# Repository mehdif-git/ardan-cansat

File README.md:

## SCALAR-VI CANSAT *Ardan*

## Description
Code and schematics of the cansat aboard SCALAR-VI made with students of the Jules Verne middleschool in Carcassone, FR.

## Installation
The ‘RadioHead’ library used to manage the LoRaWAN depends on “stdatomic”, we need to change the source code of ‘RadioHead’ to source the correct implementation for Arduino vs. ESP.

## Contributing
This work is common to the Supaero Space Section's Scalar project. Any project member is allowed to contribute.

## Authors and acknowledgment
Electronics has been made with the help of F. Topeza and C. Mopin-Rauschkolb.
CAD has been done entierly by D. Bessede

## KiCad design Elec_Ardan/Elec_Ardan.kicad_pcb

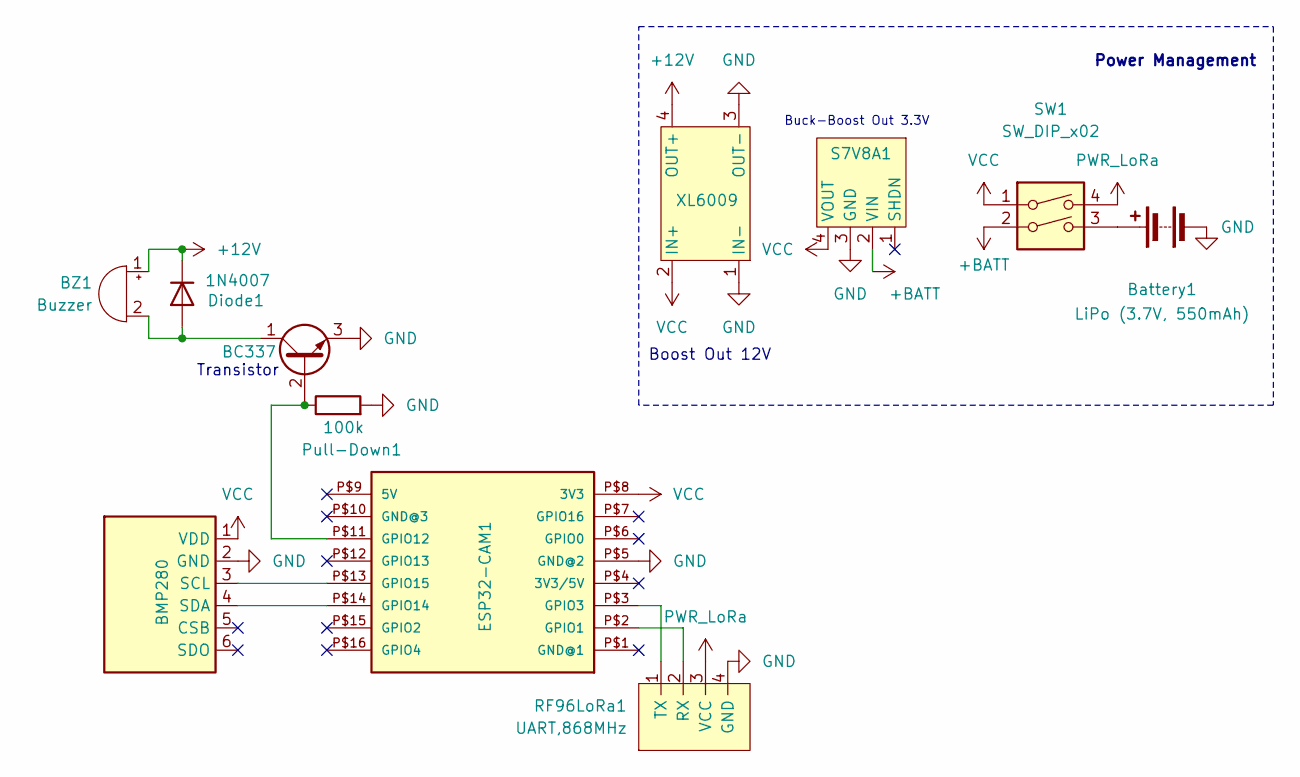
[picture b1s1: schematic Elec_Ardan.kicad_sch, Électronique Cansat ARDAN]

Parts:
BMP280: BMP280
BZ1: Buzzer; JST_XH_B2B-XH-A_1x02_P2.50mm_Vertical
Battery1: LiPo (3.7V, 550mAh); JST_XH_B2B-XH-A_1x02_P2.50mm_Vertical
Diode1: 1N4007; D_DO-41_SOD81_P10.16mm_Horizontal
ESP32-CAM1: ESP32-CAM
Pull-Down1: 100k; R_Axial_DIN0309_L9.0mm_D3.2mm_P12.70mm_Horizontal
Q1: BC337; TO-92_Inline
RF96LoRa1: UART,868MHz; JST_XH_B4B-XH-A_1x04_P2.50mm_Vertical
S7V8A1: S7V8A1
SW1: SW_DIP_x02; JST_XH_B4B-XH-A_1x04_P2.50mm_Vertical
XL6009: XL6009

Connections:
+12V: BZ1.1 (+), Diode1.1 (K), XL6009.4 (OUT+)
+BATT: S7V8A1.2 (VIN), SW1.2
GND: BMP280.2 (GND), Battery1.2 (-), ESP32-CAM1.P$5 (GND@2), Pull-Down1.2, Q1.3 (E), RF96LoRa1.4 (GND), S7V8A1.3 (GND), XL6009.1 (IN-), XL6009.3 (OUT-)
unnamed: BMP280.3 (SCL), ESP32-CAM1.P$13 (GPIO15)
unnamed: BMP280.4 (SDA), ESP32-CAM1.P$14 (GPIO14)
unnamed: BZ1.2 (-), Diode1.2 (A), Q1.1 (C)
unnamed: Battery1.1 (+), SW1.3
unnamed: ESP32-CAM1.P$2 (GPIO1), RF96LoRa1.2 (RX)
unnamed: ESP32-CAM1.P$3 (GPIO3), RF96LoRa1.1 (TX)
unnamed: ESP32-CAM1.P$11 (GPIO12), Pull-Down1.1, Q1.2 (B)
PWR_LoRa: RF96LoRa1.3 (VCC), SW1.4
VCC: BMP280.1 (VDD), ESP32-CAM1.P$8 (3V3), S7V8A1.4 (VOUT), SW1.1, XL6009.2 (IN+)

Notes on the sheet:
Power Management
Buck-Boost Out 3.3V
Boost Out 12V
Transistor

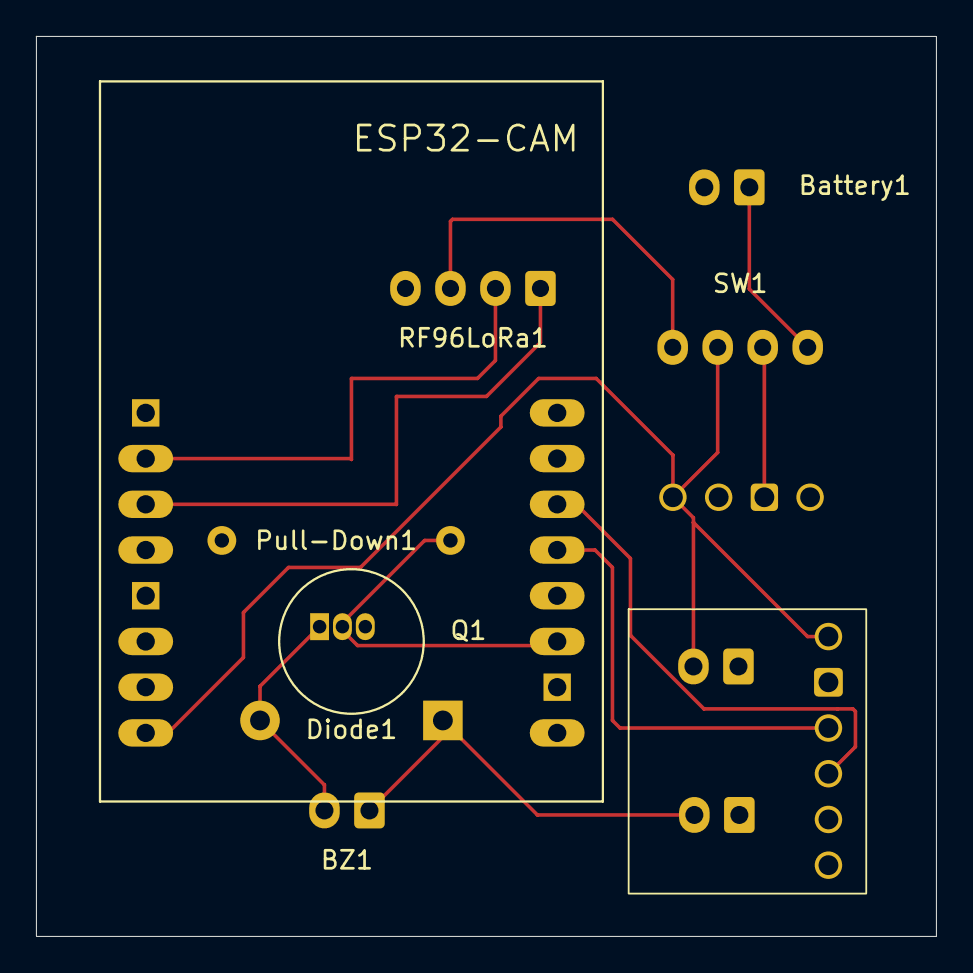
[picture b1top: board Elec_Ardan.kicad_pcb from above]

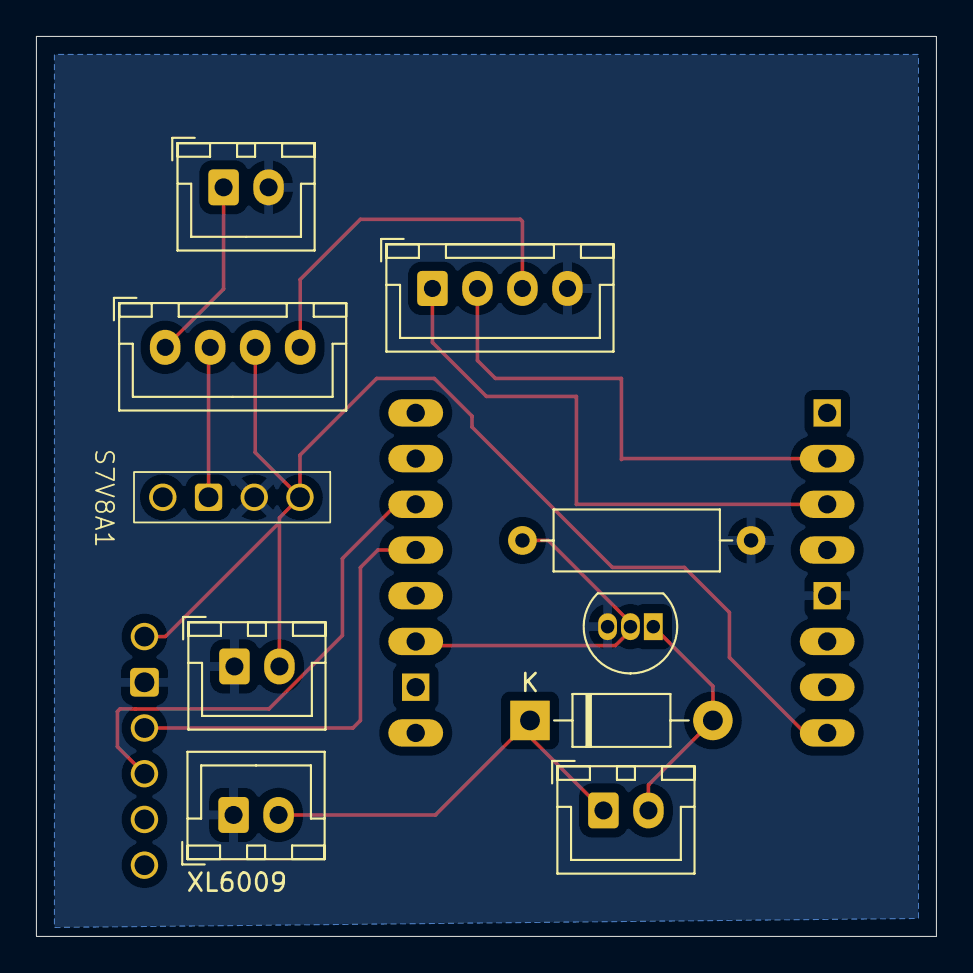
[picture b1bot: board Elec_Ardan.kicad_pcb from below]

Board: 2 copper layers, 50.0 x 50.0 mm, 11 parts (9 on the bottom side), 12 nets.

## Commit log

2025-01-27 Initial commit.
2025-01-27 Edited README with basic info.
2025-03-02 Final beta code.
2025-03-03 Arduino code.
2025-06-03 Version du projet 3 juin 2025.
2025-06-03 Ajout du fichier STEP de la carte entière
2025-06-03 Ajout de notes pour le rapport de la RCE 3.
2025-07-05 Code final
2025-07-06 Unit tests
2025-07-06 new test receiver
